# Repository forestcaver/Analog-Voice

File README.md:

# Analog-Voice

This repository will hold my analog voice modules.

The plan is to design and build a cheap analog (mainly subtractive) voice that can be built very cheaply or even
ordered via the Chinese PCB Assembly services.

Please read below for the status of these designs. Some are works in progress and some are completed.

- - - -

I made a 3d-printed case with a dc-dc converter (£7.50) to test them:

- - - -

## 3340 VCO ##

8hp.

3340-based oscillator with hard and soft sync, linear and exponential fm (with fm cv attenuverter), pulse width (knob and cv with attenuator). Reverse polarity protection. Uses an as3340 chip.

The 3340 soft sync only works on a falling edge so a ramp waveform is ideal eg /| (and not |\ ). Hard sync works on rise and fall. The sync switch is an on-off-on switch (centre position turns off sync)
The 3340 fm knob is an attenuverter. The fm switch selects between exp fm (dc coupled) and lin fm (ac coupled). It's an on-off-on switch so the centre position turns off fm (handy for wiggling). The lin fm is ideal for audio rate modulation.
The 3340 pwm input takes 0-5v for min to max effect. The pwm pot is an attenuator, pwm is added to the pw pot.
The outputs of the 3340 are all normalised to just below 10v p-p, all outputs are bipolar.
Calibration is as per the cem3340 datasheet. ie set v/oct scaling, then do the hi-osc adjustment if necessary.
Mine tracks within one cent over 6 octaves.

- - - -

## 3320 LPF ##

4hp.

4-pole (24db/oct lpf) with fm cv attenuverter, can self oscillate. Reverse polarity protection. Uses an as3320 chip.

The fm knob is an attenuverter
The 3320 has quite an aggressive resonance which kicks in at about 1/3 of the turn of the pot. You can easily adjust this by using different values for r25. One technique to find what you like could be to wire a 100k pot to the two pads, play with the module and set the resonance how you want, then desolder, read the resistance and solder a resistor of that value. You can refer to the resonance curve in the datasheet as well to see the response curve. I like it quite aggressive and have chosen about a 50k (ie 49.9k) resistor to get full range of resonance.
Calibration - turn resonance up to self-oscillation and adjust the tracking to get the best you can. It's not temperature corrected or perfect but is pretty reasonable. Before you calibrate, let it warm up for a few minutes ideally. It will track within 1 cent over two octaves.

- - - -

## Phones (Headphone Amp) ##

4hp

NJM4556 based headphone amp. This is essentially the power section from the nwavguy o2 headphone amp. It has
a very low output impedance (~1 ohm) so can drive even low impedance headphones. It can deliver a high power
(utilising two sections of the njm4556 per channel) so can drive 600 ohm impedance headphones with no problem.
There is a high pass filter on the input to block dc.

- - - -

## LPG ##

4hp

Buchla-esque lpg. Uses an analog switch ic to select between filter / lpg / vca so that a mechanicaly
simple spdt on-off-on switch can be used instead of a 3pdt mechanical switch. Filter has added resonance control.

- - - -

## HPF ##

4hp

4-pole (24db/oct hpf) with fm cv attenuverter, can self oscillate. Reverse polarity protection. Uses an as3320 chip.
Very similar to the lpf (above) with a simpler set of components around the 3320 but has similar features (apart from,
obviously, being a high pass filter!)

- - - -

## Dual ASR ##

4hp

Dual ASR (Attack/Sustain/Release) in 4hp. Gate A normalled to Gate B. Reverse polarity protection. Uses two as3310 chips.

- - - -

## Dual VCA ##

4hp

Dual VCA in 4hp. (Derived from two sections of Mutable Instruments Veils). Can chain an unlimited number together to make a huge multi-channel VCA or VC-mixer. Uses a 2164 chip.

- - - -

## Wasp ##

4hp

Wasp filter in 4hp.

- - - -

## ADSR ##

4hp

a100m ADSR in 4hp.

- - - -

## LPF 2 ##

4hp

ssi2144-based filter in 4hp with attenuverter on FM input.

- - - -

## Module Tester Module ##

SMT module tester module with four added precision voltage outputs (set with trimmers).

- - - -

## Dual polarising VCA ##

4hp

Dual polarising VCA (based on Mutable Instruments Blinds). Multiple modules can be chained together.

- - - -

## Matrix Mixer ##

14hp

Matrix mixer in 4hp. Control knobs for each column can be selected to be bipolar (attenuverting) or unipolar (attenuating).
You can select a 5v offset to be normalled to input 4 as well.

- - - -
 
## TZFM VCO ##

8hp

TZFM analog VCO using the ssi2130 analog chip. Hard/soft sync (can be turned off with switch in middle position.
PWM attenuator (0-5v cv input), exponential FM with attenuverter, linear FM with attenuator. Hard/soft sync.
Jumpers allow you to change the behaviour of PWM (either the leading edge of the pulse is constant and the trailing edge
occurs at varying times or both leading and trailing edges of the pulse change). Jumpers also selct whether to use FM or PM.
(Note that this is quite a dense build!)

- - - -

## My Other Modules On GitHub ##

### Minx ###

4hp buffered mult (three sections from MI Links)

[Minx](https://github.com/forestcaver/Minx_AJH "Minx_AJH")

### Jinx ###

4hp triple S+H/noise

[Jinx](https://github.com/forestcaver/Jinx "Jinx")

### Benjolin ###

0603 version of Rob Hordijk's Benjolin (with kind permission from Rob)

Strictly for non-commercial use:

[benjolin](https://github.com/forestcaver/Benjolin "Benjolin")

- - - -

## Planned Modules ##
### Completed - not yet uploaded ###
- TZFM VCO (8hp, ssi2130-based) + 8hp expander

### In Design and Prototyping ###
- Serge volatage-controlled slew (testing now)
- MIDI Thru box
- Contact mic preamp
- Quad digital lfo and envelope generator
- vca (3360)
- vcadsr (3310)
- Wavefolder
- Distortion module
- Delay module
- Updated Benjolin

### Planned ###
- quad adsr (3310)

Licence: CC-BY-NC-SA 4.0, unless otherwise stated in the individual repositories

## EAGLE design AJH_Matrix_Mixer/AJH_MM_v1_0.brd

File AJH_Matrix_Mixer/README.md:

Matrix Mixer

Built and tested

CC-BY-NC-SA 4.0

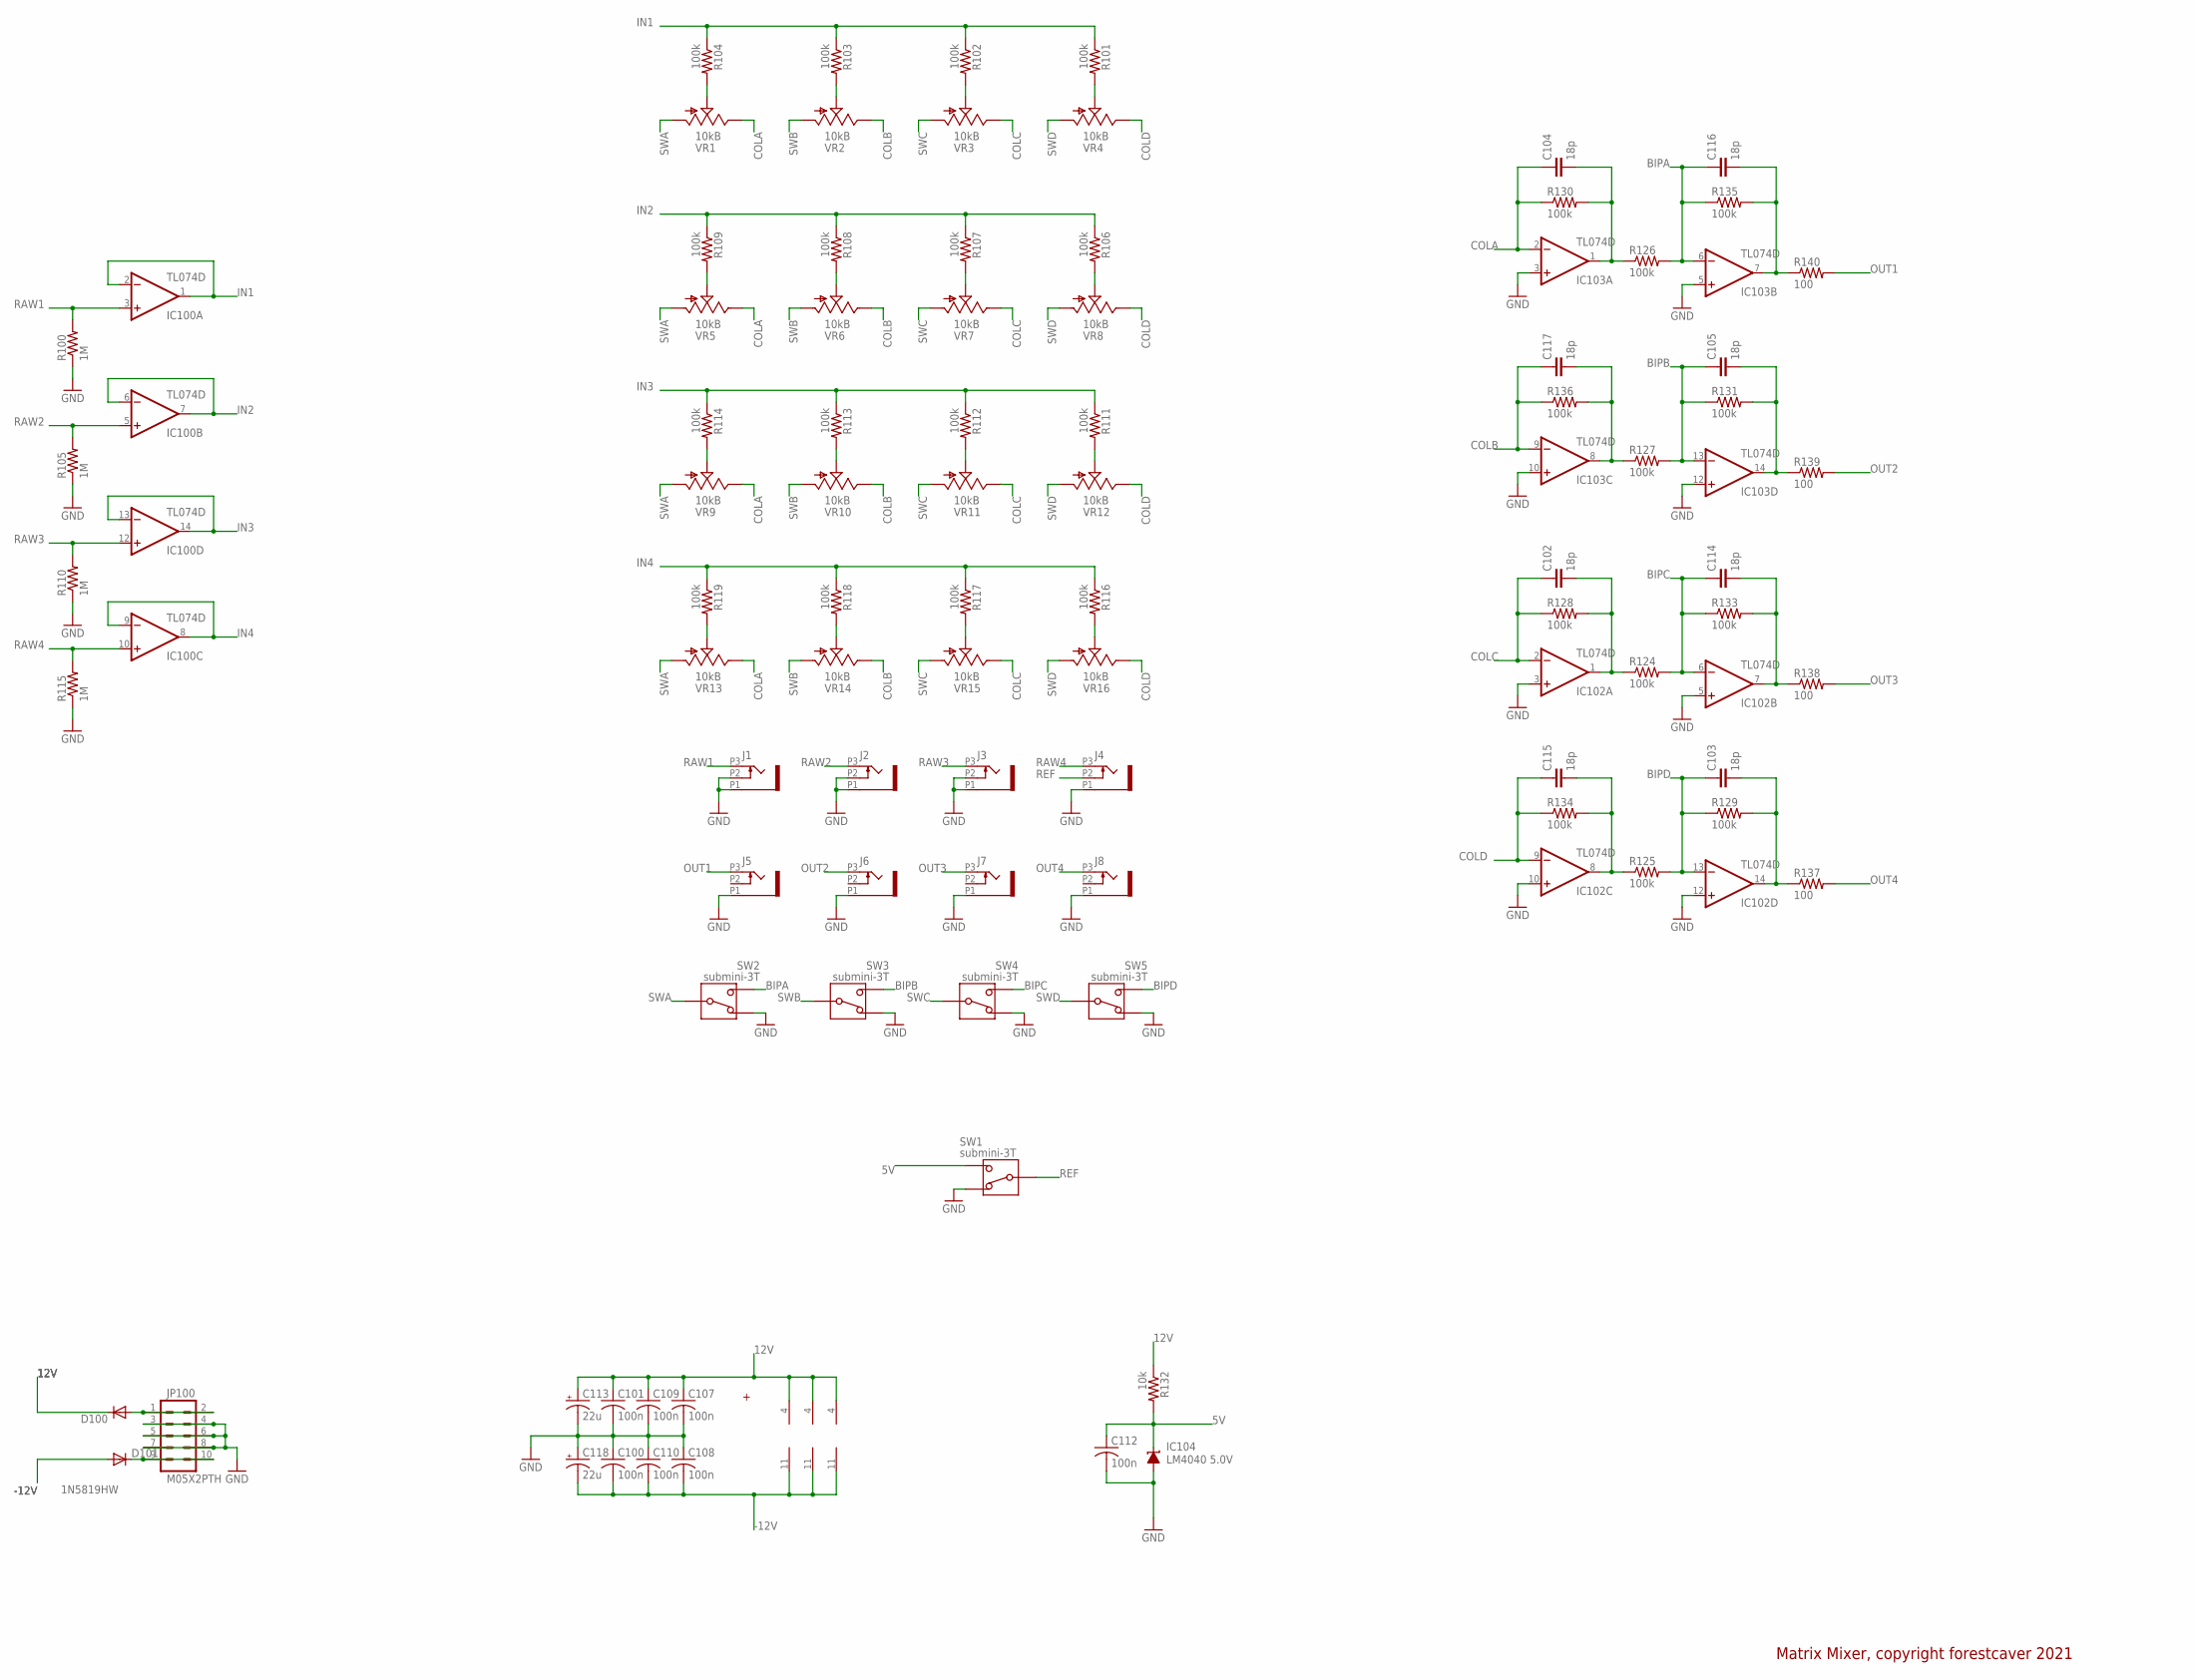
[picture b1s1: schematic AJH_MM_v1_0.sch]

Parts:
C100, C101, C107, C108, C109, C110, C112: 100n; C0603
C102, C103, C104, C105, C114, C115, C116, C117: 18p; C0603
C113, C118: 22u; PANASONIC_B
D100, D101: 1N5819HW; SOD123
IC100, IC102, IC103: TL074D; SO14
IC104: LM4040 5.0V; DBZ_R-PDSO-G3
J1, J2, J3, J4, J5, J6, J7, J8: PJ301_THONKICONN6; WQP_PJ_301M6
JP100: M05X2PTH; AVR_ICSP
R100, R105, R110, R115: 1M; R0603
R101, R102, R103, R104, R106, R107, R108, R109, R111, R112, R113, R114, R116, R117, R118, R119, R124, R125, R126, R127, R128, R129, R130, R131, R133, R134, R135, R136: 100k; R0603
R132: 10k; R0603
R137, R138, R139, R140: 100; R0603
SW1, SW2, SW3, SW4, SW5: submini-3T; SPDT-SUB
VR1, VR2, VR3, VR4, VR5, VR6, VR7, VR8, VR9, VR10, VR11, VR12, VR13, VR14, VR15, VR16: 10kB; ALPS_POT_VERTICAL

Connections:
5V: C112.1, IC104.1 (C), R132.2, SW1.P$1
12V: C101.1, C107.1, C109.1, C113.+, D100.C, IC100.4 (V+), IC102.4 (V+), IC103.4 (V+), R132.1
-12V: C100.2, C108.2, C110.2, C118.-, D101.A, IC100.11 (V-), IC102.11 (V-), IC103.11 (V-)
BIPA: C116.1, IC103.6 (-IN), R126.2, R135.1, SW2.P$1
BIPB: C105.1, IC103.13 (-IN), R127.2, R131.1, SW3.P$1
BIPC: C114.1, IC102.6 (-IN), R124.2, R133.1, SW4.P$1
BIPD: C103.1, IC102.13 (-IN), R125.2, R129.1, SW5.P$1
COLA: C104.1, IC103.2 (-IN), R130.1, VR1.P$1 (E), VR5.P$1 (E), VR9.P$1 (E), VR13.P$1 (E)
COLB: C117.1, IC103.9 (-IN), R136.1, VR2.P$1 (E), VR6.P$1 (E), VR10.P$1 (E), VR14.P$1 (E)
COLC: C102.1, IC102.2 (-IN), R128.1, VR3.P$1 (E), VR7.P$1 (E), VR11.P$1 (E), VR15.P$1 (E)
COLD: C115.1, IC102.9 (-IN), R134.1, VR4.P$1 (E), VR8.P$1 (E), VR12.P$1 (E), VR16.P$1 (E)
GND: C100.1, C101.2, C107.2, C108.1, C109.2, C110.1, C112.2, C113.-, C118.+, IC102.3 (+IN), IC102.5 (+IN), IC102.10 (+IN), IC102.12 (+IN), IC103.3 (+IN), IC103.5 (+IN), IC103.10 (+IN), IC103.12 (+IN), IC104.2 (A), J1.P1 (1), J1.P2 (2), J2.P1 (1), J2.P2 (2), J3.P1 (1), J3.P2 (2), J4.P1 (1), J5.P1 (1), J6.P1 (1), J7.P1 (1), J8.P1 (1), JP100.3, JP100.4, JP100.5, JP100.6, JP100.7, JP100.8, R100.1, R105.1, R110.1, R115.1, SW1.P$3, SW2.P$3, SW3.P$3, SW4.P$3, SW5.P$3
IN1: IC100.1 (OUT), IC100.2 (-IN), R101.1, R102.1, R103.1, R104.1
IN2: IC100.6 (-IN), IC100.7 (OUT), R106.1, R107.1, R108.1, R109.1
IN3: IC100.13 (-IN), IC100.14 (OUT), R111.1, R112.1, R113.1, R114.1
IN4: IC100.8 (OUT), IC100.9 (-IN), R116.1, R117.1, R118.1, R119.1
unnamed: R104.2, VR1.P$2 (S)
unnamed: R103.2, VR2.P$2 (S)
unnamed: R102.2, VR3.P$2 (S)
unnamed: R101.2, VR4.P$2 (S)
unnamed: D100.A, JP100.1, JP100.2
unnamed: R114.2, VR9.P$2 (S)
unnamed: C117.2, IC103.8 (OUT), R127.1, R136.2
unnamed: R113.2, VR10.P$2 (S)
unnamed: R112.2, VR11.P$2 (S)
unnamed: R111.2, VR12.P$2 (S)
unnamed: C104.2, IC103.1 (OUT), R126.1, R130.2
unnamed: R119.2, VR13.P$2 (S)
unnamed: R118.2, VR14.P$2 (S)
unnamed: R117.2, VR15.P$2 (S)
unnamed: R116.2, VR16.P$2 (S)
unnamed: C116.2, IC103.7 (OUT), R135.2, R140.1
unnamed: D101.C, JP100.9, JP100.10
unnamed: C105.2, IC103.14 (OUT), R131.2, R139.1
unnamed: R109.2, VR5.P$2 (S)
unnamed: R108.2, VR6.P$2 (S)
unnamed: C102.2, IC102.1 (OUT), R124.1, R128.2
unnamed: C114.2, IC102.7 (OUT), R133.2, R138.1
unnamed: C115.2, IC102.8 (OUT), R125.1, R134.2
unnamed: C103.2, IC102.14 (OUT), R129.2, R137.1
unnamed: R107.2, VR7.P$2 (S)
unnamed: R106.2, VR8.P$2 (S)
OUT1: J5.P3 (3), R140.2
OUT2: J6.P3 (3), R139.2
OUT3: J7.P3 (3), R138.2
OUT4: J8.P3 (3), R137.2
RAW1: IC100.3 (+IN), J1.P3 (3), R100.2
RAW2: IC100.5 (+IN), J2.P3 (3), R105.2
RAW3: IC100.12 (+IN), J3.P3 (3), R110.2
RAW4: IC100.10 (+IN), J4.P3 (3), R115.2
REF: J4.P2 (2), SW1.P$2
SWA: SW2.P$2, VR1.P$3 (A), VR5.P$3 (A), VR9.P$3 (A), VR13.P$3 (A)
SWB: SW3.P$2, VR2.P$3 (A), VR6.P$3 (A), VR10.P$3 (A), VR14.P$3 (A)
SWC: SW4.P$2, VR3.P$3 (A), VR7.P$3 (A), VR11.P$3 (A), VR15.P$3 (A)
SWD: SW5.P$2, VR4.P$3 (A), VR8.P$3 (A), VR12.P$3 (A), VR16.P$3 (A)

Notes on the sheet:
Matrix Mixer, copyright forestcaver 2021

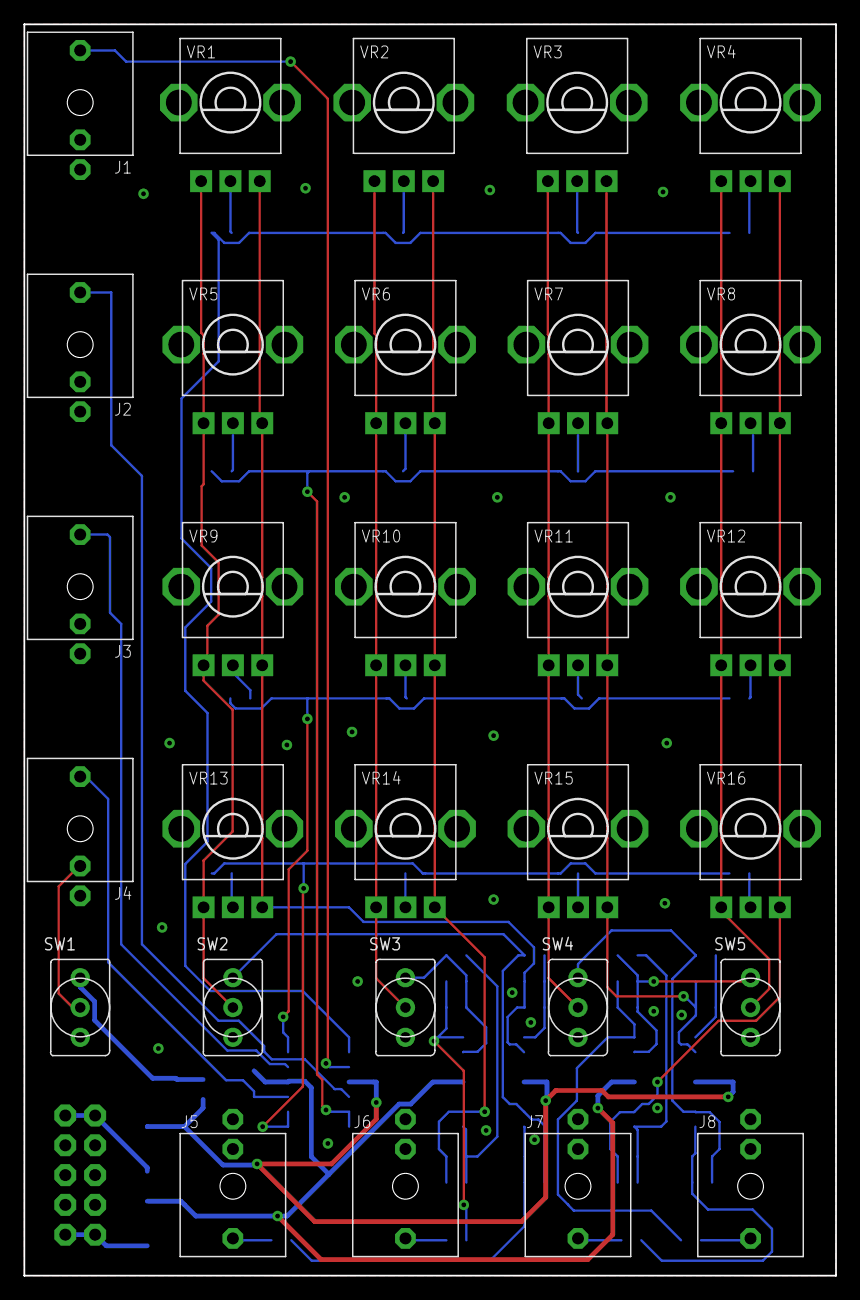
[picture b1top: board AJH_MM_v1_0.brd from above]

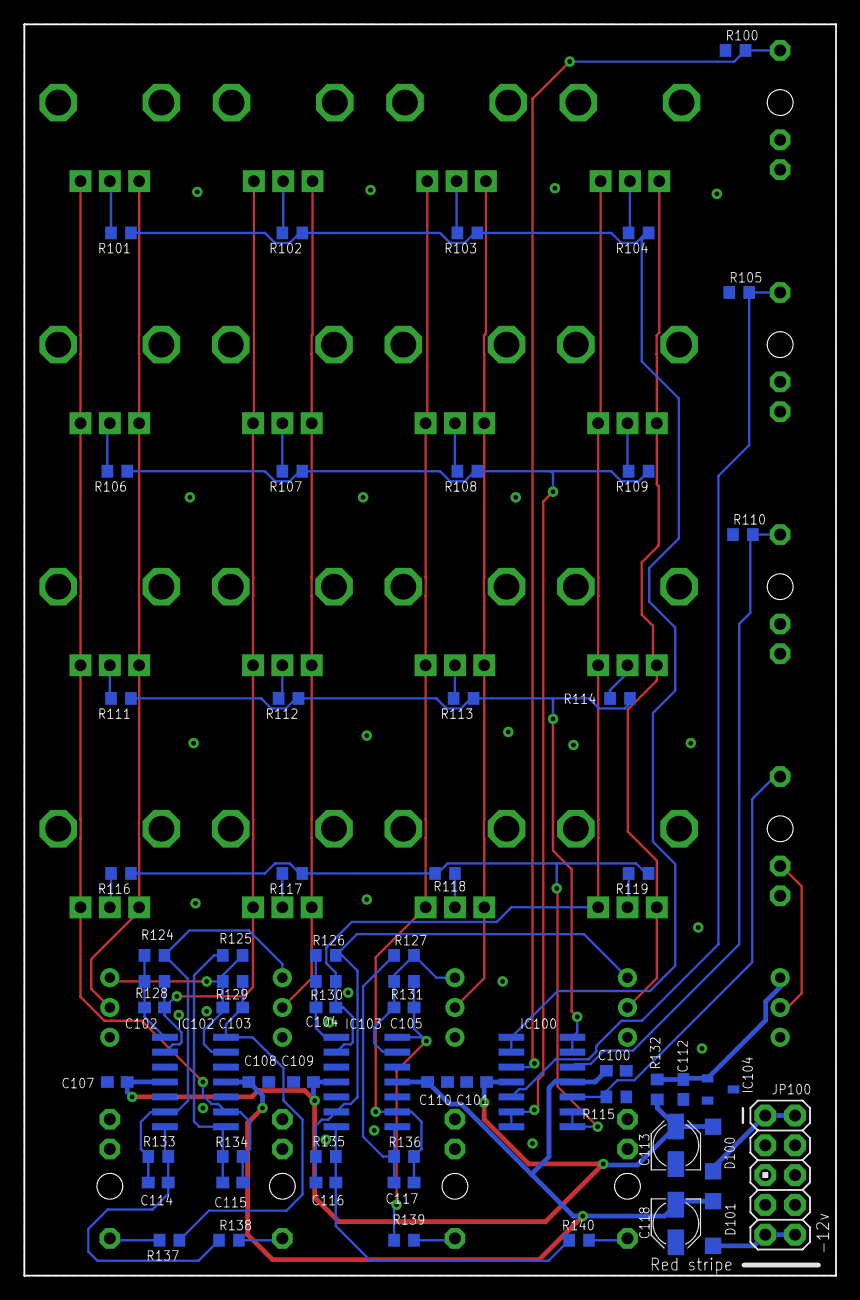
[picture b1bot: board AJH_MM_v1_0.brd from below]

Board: 2 copper layers, 69.2 x 106.7 mm, 90 parts (61 on the bottom side), 55 nets.

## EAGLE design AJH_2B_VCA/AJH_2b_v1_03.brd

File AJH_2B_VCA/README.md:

# 2B_VCA

Two sections of Mutable Instruments Blinds. Multipe modules can be
chained together.

Tested and working.

CC-By-SA-4.0

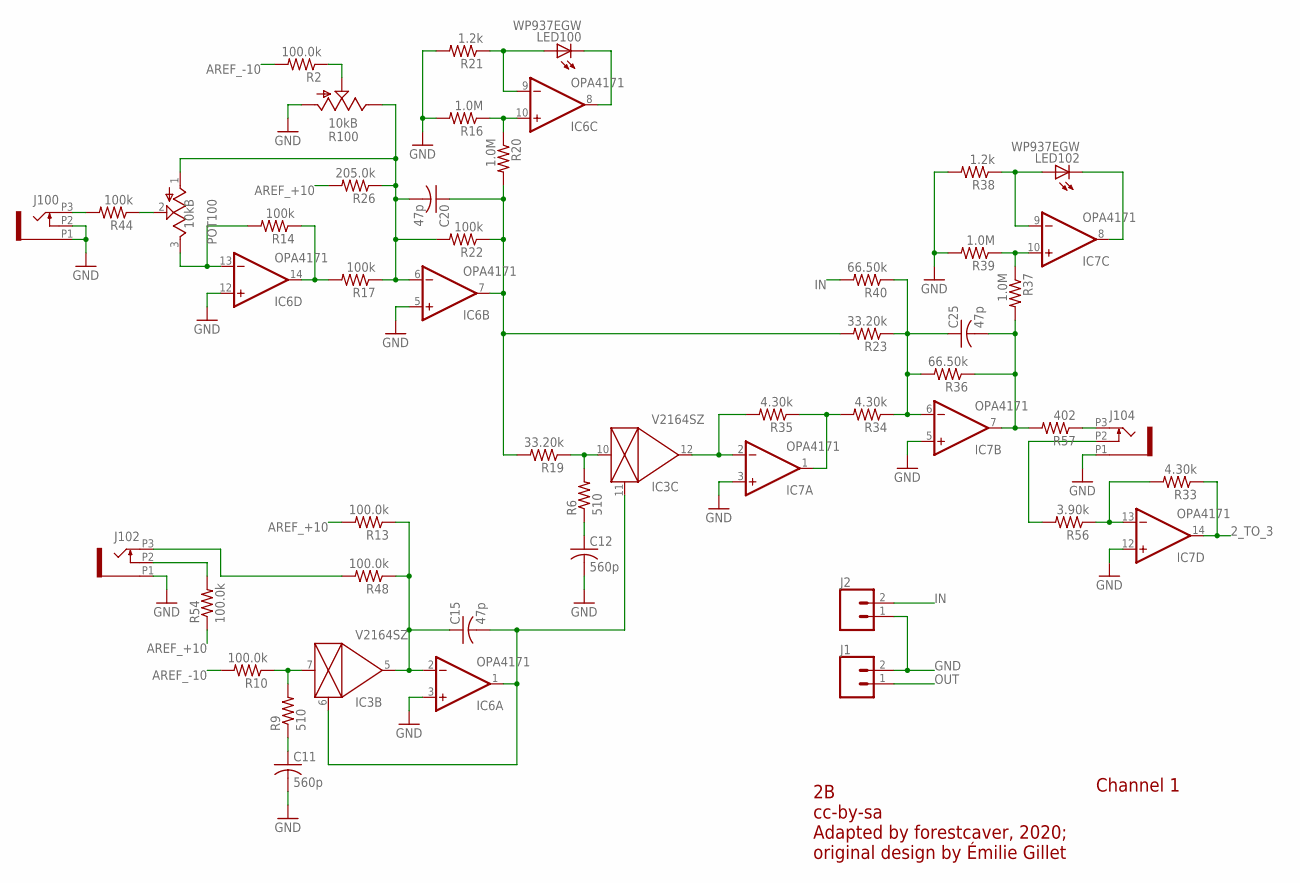
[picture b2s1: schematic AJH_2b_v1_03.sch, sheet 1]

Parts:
C11, C12: 560p; C0402
C15, C20, C25: 47p; C0402
IC3: V2164SZ; SOIC16N
IC6, IC7: OPA4171; TSSOP14
J1, J2: CONN_02; 1X02
J100, J102, J104: PJ301_THONKICONN6; WQP_PJ_301M6
LED100, LED102: WP937EGW; LED3MM
POT100: 10kB; ALPS_POT_NOHOLE
R2, R10, R13, R48, R54: 100.0k; R0402
R6, R9: 510; R0402
R14, R17, R22, R44: 100k; R0402
R16, R20, R37, R39: 1.0M; R0402
R19, R23: 33.20k; R0402
R21, R38: 1.2k; R0402
R26: 205.0k; R0402
R33, R34, R35: 4.30k; R0402
R36, R40: 66.50k; R0402
R56: 3.90k; R0402
R57: 402; R0402
R100: 10kB; ALPS_POT_VERTICAL_PS

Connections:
2_TO_3: IC7.14 (OUT), R33.1; also elsewhere on the board
AREF_+10: R13.2, R26.2, R54.1; also elsewhere on the board
AREF_-10: R2.2, R10.2; also elsewhere on the board
FOO1: IC3.7 (IN), R9.2, R10.1
GAIN_2: C20.1, IC6.7 (OUT), R19.2, R20.2, R22.1, R23.2
GND: C11.2, C12.2, IC6.3 (+IN), IC6.5 (+IN), IC6.12 (+IN), IC7.3 (+IN), IC7.5 (+IN), IC7.12 (+IN), J1.2, J2.1, J100.P1 (1), J100.P2 (2), J102.P1 (1), J104.P1 (1), R16.2, R21.2, R38.2, R39.2, R100.P$3 (A); also elsewhere on the board
IN: J2.2, R40.2
unnamed: J104.P3 (3), R57.1
unnamed: C12.1, R6.1
unnamed: IC3.10 (IN), R6.2, R19.1
unnamed: IC3.12 (OUT), IC7.2 (-IN), R35.2
unnamed: C25.1, IC7.6 (-IN), R23.1, R34.1, R36.2, R40.1
unnamed: J100.P3 (3), R44.2
unnamed: IC6.13 (-IN), POT100.3 (B), R14.2
unnamed: IC6.14 (OUT), R14.1, R17.2
unnamed: C20.2, IC6.6 (-IN), POT100.1 (A), R17.1, R22.2, R26.1, R100.P$1 (E)
unnamed: R2.1, R100.P$2 (S)
unnamed: IC6.8 (OUT), LED100.K (C)
unnamed: IC6.9 (-IN), LED100.A, R21.1
unnamed: IC7.8 (OUT), LED102.K (C)
unnamed: IC7.9 (-IN), LED102.A, R38.1
unnamed: IC7.13 (-IN), R33.2, R56.1
unnamed: J104.P2 (2), R56.2
unnamed: IC7.1 (OUT), R34.2, R35.1
unnamed: POT100.2 (W), R44.1
unnamed: C11.1, R9.1
unnamed: C15.1, IC3.5 (OUT), IC6.2 (-IN), R13.1, R48.1
unnamed: C15.2, IC3.6 (CTRL), IC3.11 (CTRL), IC6.1 (OUT)
unnamed: J102.P3 (3), R48.2
unnamed: J102.P2 (2), R54.2
unnamed: IC7.10 (+IN), R37.1, R39.1
unnamed: IC6.10 (+IN), R16.1, R20.1
OUT: J1.1; also elsewhere on the board
OUT2: C25.2, IC7.7 (OUT), R36.1, R37.2, R57.2

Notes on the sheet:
Channel 1
2B cc-by-sa Adapted by forestcaver, 2020; original design by Émilie Gillet

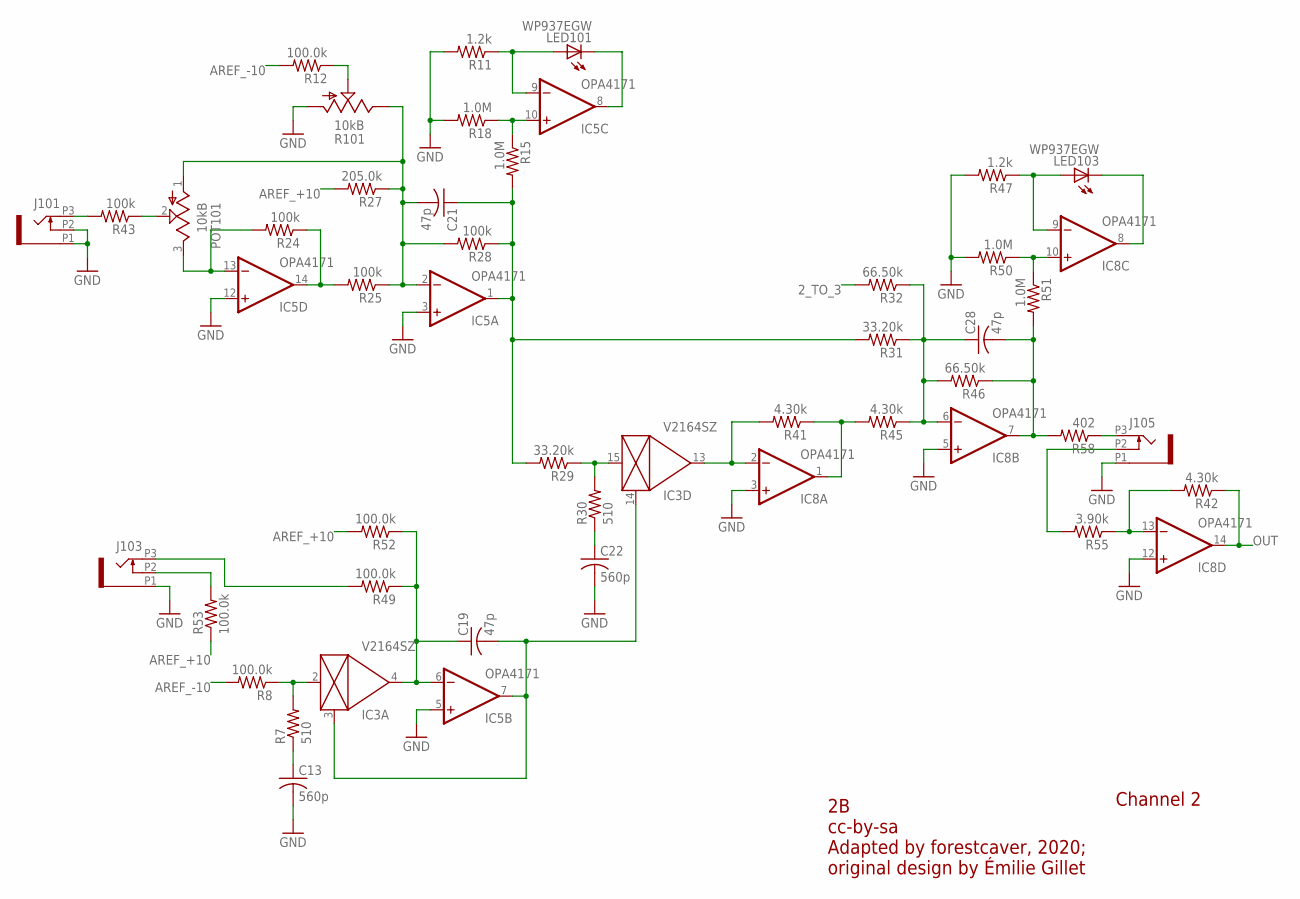
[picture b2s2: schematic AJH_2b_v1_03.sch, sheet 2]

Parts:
C13, C22: 560p; C0402
C19, C21, C28: 47p; C0402
IC3: V2164SZ; SOIC16N
IC5, IC8: OPA4171; TSSOP14
J101, J103, J105: PJ301_THONKICONN6; WQP_PJ_301M6
LED101, LED103: WP937EGW; LED3MM
POT101: 10kB; ALPS_POT_NOHOLE
R7, R30: 510; R0402
R8, R12, R49, R52, R53: 100.0k; R0402
R11, R47: 1.2k; R0402
R15, R18, R50, R51: 1.0M; R0402
R24, R25, R28, R43: 100k; R0402
R27: 205.0k; R0402
R29, R31: 33.20k; R0402
R32, R46: 66.50k; R0402
R41, R42, R45: 4.30k; R0402
R55: 3.90k; R0402
R58: 402; R0402
R101: 10kB; ALPS_POT_VERTICAL_PS

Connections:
2_TO_3: R32.2; also elsewhere on the board
AREF_+10: R27.2, R52.2, R53.1; also elsewhere on the board
AREF_-10: R8.2, R12.2; also elsewhere on the board
FOO2: IC3.2 (IN), R7.2, R8.1
GAIN_3: C21.1, IC5.1 (OUT), R15.2, R28.1, R29.2, R31.2
GND: C13.2, C22.2, IC5.3 (+IN), IC5.5 (+IN), IC5.12 (+IN), IC8.3 (+IN), IC8.5 (+IN), IC8.12 (+IN), J101.P1 (1), J101.P2 (2), J103.P1 (1), J105.P1 (1), R11.2, R18.2, R47.2, R50.2, R101.P$3 (A); also elsewhere on the board
unnamed: J105.P3 (3), R58.1
unnamed: C22.1, R30.1
unnamed: IC3.15 (IN), R29.1, R30.2
unnamed: IC3.13 (OUT), IC8.2 (-IN), R41.2
unnamed: C28.1, IC8.6 (-IN), R31.1, R32.1, R45.1, R46.2
unnamed: J101.P3 (3), R43.2
unnamed: IC5.13 (-IN), POT101.3 (B), R24.2
unnamed: IC5.14 (OUT), R24.1, R25.2
unnamed: C21.2, IC5.2 (-IN), POT101.1 (A), R25.1, R27.1, R28.2, R101.P$1 (E)
unnamed: R12.1, R101.P$2 (S)
unnamed: IC5.8 (OUT), LED101.K (C)
unnamed: IC5.9 (-IN), LED101.A, R11.1
unnamed: IC8.8 (OUT), LED103.K (C)
unnamed: IC8.9 (-IN), LED103.A, R47.1
unnamed: IC8.13 (-IN), R42.2, R55.1
unnamed: J105.P2 (2), R55.2
unnamed: IC8.1 (OUT), R41.1, R45.2
unnamed: C13.1, R7.1
unnamed: C19.1, IC3.4 (OUT), IC5.6 (-IN), R49.1, R52.1
unnamed: C19.2, IC3.3 (CTRL), IC3.14 (CTRL), IC5.7 (OUT)
unnamed: POT101.2 (W), R43.1
unnamed: J103.P3 (3), R49.2
unnamed: J103.P2 (2), R53.2
unnamed: IC8.10 (+IN), R50.1, R51.1
unnamed: IC5.10 (+IN), R15.1, R18.1
OUT: IC8.14 (OUT), R42.1; also elsewhere on the board
OUT3: C28.2, IC8.7 (OUT), R46.1, R51.2, R58.2

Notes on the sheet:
Channel 2
2B cc-by-sa Adapted by forestcaver, 2020; original design by Émilie Gillet

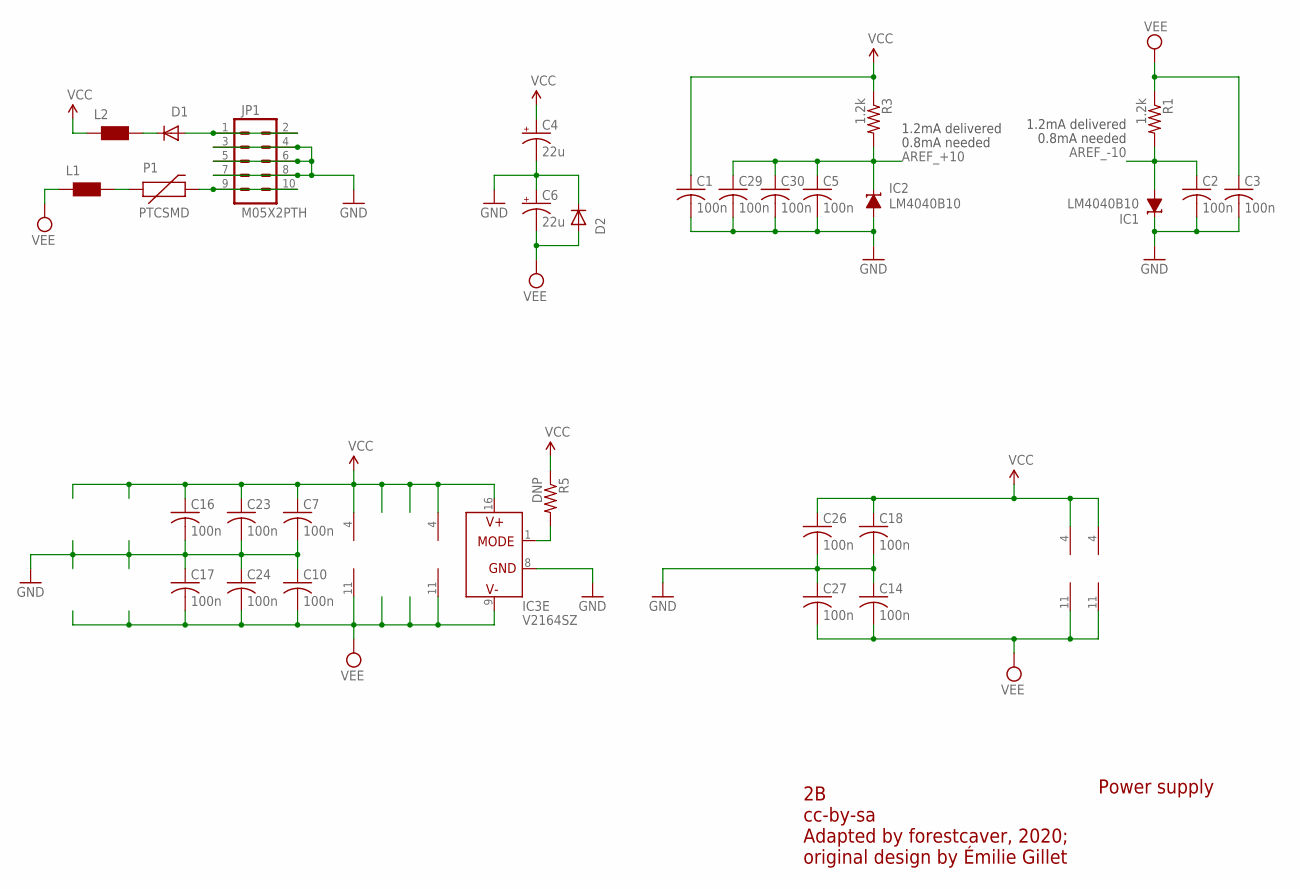
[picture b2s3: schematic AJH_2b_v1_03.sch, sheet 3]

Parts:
C1, C2, C3, C5, C7, C10, C14, C16, C17, C18, C23, C24, C26, C27, C29, C30: 100n; C0402
C4, C6: 22u; PANASONIC_B
D1, D2: 1N5819HW; SOD123
IC1, IC2: LM4040B10; DBZ_R-PDSO-G3
IC3: V2164SZ; SOIC16N
IC5, IC6, IC7, IC8: OPA4171; TSSOP14
JP1: M05X2PTH; AVR_ICSP
L1, L2: WE-CBF_0603; 0603
P1: PTCSMD; PTC-1206
R1, R3: 1.2k; R0402
R5: DNP; R0402

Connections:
AREF_+10: C5.1, C29.1, C30.1, IC2.1 (C), R3.2; also elsewhere on the board
AREF_-10: C2.1, IC1.2 (A), R1.2; also elsewhere on the board
GND: C1.2, C2.2, C3.2, C4.-, C5.2, C6.+, C7.2, C10.1, C14.1, C16.2, C17.1, C18.2, C23.2, C24.1, C26.2, C27.1, C29.2, C30.2, D2.C, IC1.1 (C), IC2.2 (A), IC3.8 (GND), JP1.3, JP1.4, JP1.5, JP1.6, JP1.7, JP1.8; also elsewhere on the board
unnamed: IC3.1 (MODE), R5.2
unnamed: D1.A, JP1.1, JP1.2
unnamed: JP1.9, JP1.10, P1.2
unnamed: L1.2, P1.1
unnamed: D1.C, L2.2
VCC: C1.1, C4.+, C7.1, C16.1, C18.1, C23.1, C26.1, IC3.16 (V+), IC5.4 (V+), IC6.4 (V+), IC7.4 (V+), IC8.4 (V+), L2.1, R3.1, R5.1
VEE: C3.1, C6.-, C10.2, C14.2, C17.2, C24.2, C27.2, D2.A, IC3.9 (V-), IC5.11 (V-), IC6.11 (V-), IC7.11 (V-), IC8.11 (V-), L1.1, R1.1

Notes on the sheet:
Power supply
1.2mA delivered
0.8mA needed
2B cc-by-sa Adapted by forestcaver, 2020; original design by Émilie Gillet

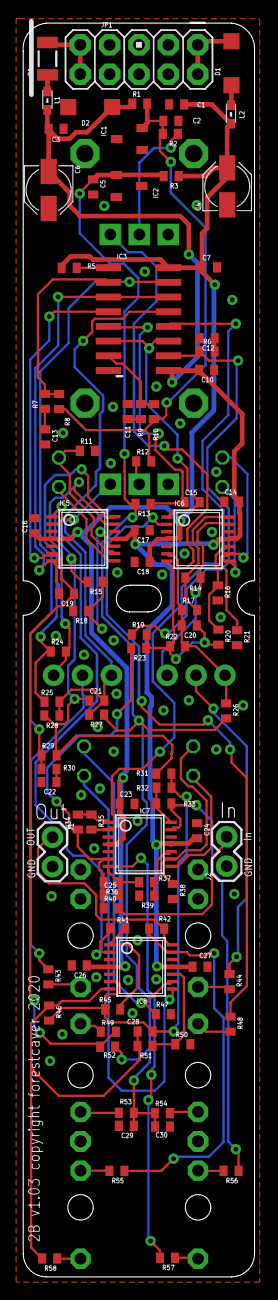
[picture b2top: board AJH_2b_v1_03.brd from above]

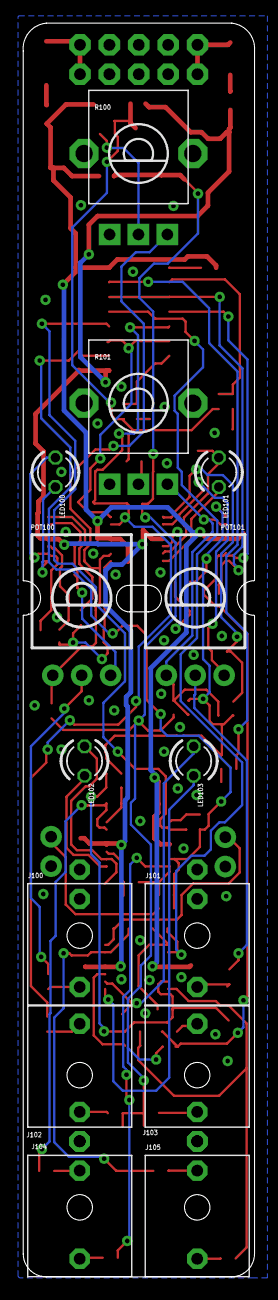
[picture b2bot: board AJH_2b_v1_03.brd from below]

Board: 2 copper layers, 20.0 x 108.4 mm, 114 parts (14 on the bottom side), 69 nets.

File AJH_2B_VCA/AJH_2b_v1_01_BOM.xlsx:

AJH_2b_v1_00_BOM
Qty | Value | Device | Package | Parts | Notes | Description | Mouser
2 |  | CONN_02 | 1X02 | J1, J2 | 2x1 2.54mm male | Multi connection point. Often used as Generic Header-pin footprint for 0.1 inch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 | 571-5-146135-4
2 |  | WE-CBF_0603 | 603 | L1, L2 | ferrite | SMD EMI Suppression Ferrite Beads | 710-742792664
8 | 1.0M | R-US_R0402 | R0402 | R15, R16, R18, R20, R37, R39, R50, R51 | 0.01 | RESISTOR, American symbol | 667-ERJ-2RKF1004X
6 | 1.2k | R-US_R0402 | R0402 | R1, R3, R11, R21, R38, R47 | 0.01 | RESISTOR, American symbol | 667-ERJ-2RKF1201X
10 | 100.0k | R-US_R0402 | R0402 | R2, R8, R10, R12, R13, R48, R49, R52, R53, R54 |  | RESISTOR, American symbol | 667-ERA-2AEB104X
8 | 100k | R-US_R0402 | R0402 | R14, R17, R22, R24, R25, R28, R43, R44 | 0.01 | RESISTOR, American symbol | ERJ-2RKF1003X
18 | 100n | C-USC0402 | C0402 | C1, C2, C3, C5, C7, C8, C9, C10, C14, C16, C17, C18, C23, C24, C26, C27, C29, C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 | >= 25V | CAPACITOR, American symbol | 81-GRM155R61E104KA7D
2 | 10kB | POT_USVERTICAL_PS | ALPS_POT_VERTICAL_PS | R100, R101 | 9mm Alpha pot | 9mm Alpha pot | www,thonk.co.uk
2 | 10kB | POT_VERTICALNOHOLE | ALPS_POT_NOHOLE | POT100, POT101 | 9mm tall trimmer | tall trimmer 9mm | www,thonk.co.uk
2 | 1N5819HW | DIODE-SOD123 | SOD123 | D1, D2 | schottky | DIODE | 621-1N5819HW-F
2 | 205.0k | R-US_R0402 | R0402 | R26, R27 | 0.001 | RESISTOR, American symbol | 279-RP73PF1E205KBTDF
2 | 22u | CPOL-USB | PANASONIC_B | C4, C6 | >= 25V | POLARIZED CAPACITOR, American symbol | 667-EEE-FT1V220AR
2 | 3.90k | R-US_R0402 | R0402 | R55, R56 | 0.001 | RESISTOR, American symbol | 667-ERA-2AEB392X
4 | 33.20k | R-US_R0402 | R0402 | R19, R23, R29, R31 | 0.001 | RESISTOR, American symbol | 667-ERA-2AEB3322X
6 | 4.30k | R-US_R0402 | R0402 | R33, R34, R35, R41, R42, R45 | 0.001 | RESISTOR, American symbol | 667-ERA-2AEB432X
2 | 402 | R-US_R0402 | R0402 | R57, R58 | 0.01 | RESISTOR, American symbol | 667-ERJ-2RKF4020X
6 | 47p | C-USC0402 | C0402 | C15, C19, C20, C21, C25, C28 | >= 50V, 1%, C0G | CAPACITOR, American symbol | 81-GRM1555C1H470JA1D
4 | 510 | R-US_R0402 | R0402 | R6, R7, R9, R30 | 0.01 | RESISTOR, American symbol | 667-ERJ-2RKF5100X
4 | 560p | C-USC0402 | C0402 | C11, C12, C13, C22 | >= 25V, 5%, C0G | CAPACITOR, American symbol | 81-GRM1555C1E561JA1D
4 | 66.50k | R-US_R0402 | R0402 | R32, R36, R40, R46 | 0.001 | RESISTOR, American symbol | 667-ERA-2AEB6652X
2 | DNP | R-US_R0402 | R0402 | R4, R5 | DNP | RESISTOR, American symbol
2 | LM4040B10 | LM4041B12DBZ | DBZ_R-PDSO-G3 | IC1, IC2 | 0.002 | PRECISION MICROPOWER SHUNT VOLTAGE REFERENCE | 595-LM4040B10IDBZR
1 | M05X2PTH | M05X2PTH | AVR_ICSP | JP1 | 5x2 2.54mm male | Header 5x2 | 649-67996-410HLF
4 | OPA4171 | TL074PW | TSSOP14 | IC5, IC6, IC7, IC8 | TSSOP14 | OP AMP | 595-OPA4171AIPWR
6 | PJ301_THONKICONN6 | PJ301_THONKICONN6 | WQP_PJ_301M6 | J100, J101, J102, J103, J104, J105 | Thonkiconn |  | www,thonk.co.uk
1 | PTCSMD | PTCSMD | PTC-1206 | P1 | >= 15V, >0.1A | Resettable Fuse PTC | 576-1206L035/16YR
2 | V2164SZ | SSM2164S | SOIC16N | IC3, IC4 | 2164 |  | www,thonk.co.uk
4 | WP937EGW | LED3MM | LED3MM | LED100, LED101, LED102, LED103 | 3mm bipolar LED | LED | 604-WP937EGW

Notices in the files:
AJH_LPG/lpg_v22_4hp.brd:
LPG v1.2 by forestcaver,
copyright 2020
parts and their libraries:
SparkFun-Connectors: Licensing: Creative Commons ShareAlike 4.0 International - https://creativecommons.org/licenses/by-sa/4.0
